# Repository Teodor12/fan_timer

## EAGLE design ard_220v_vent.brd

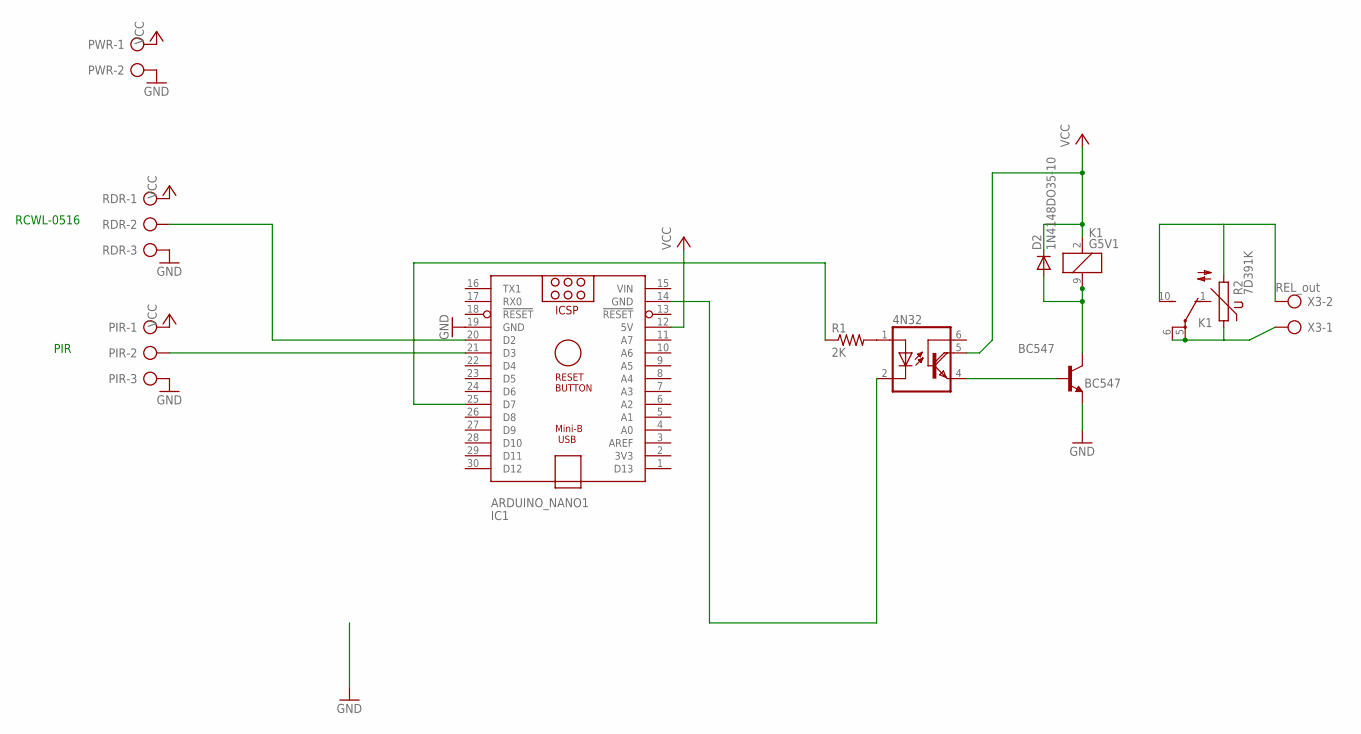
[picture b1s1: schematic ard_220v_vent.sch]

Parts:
4N32: 4N33; DIL06; MPN 4N32
ARDUINO_NANO1: IC1; ARDUINO_NANO
BC547: BC547; TO92
D2: 1N4148DO35-10; DO35-10
K1: G5V1
PIR: AK500/3
PWR: AK500/2
R1: 2K; 0207/10
R2: 7D391K; S07K385
RDR: AK500/3
X3: REL_out; AK500/2

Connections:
GND: ARDUINO_NANO1.19 (GND), BC547.1 (E), PIR.3, PWR.2, RDR.3
unnamed: BC547.3 (C), D2.A, K1.9 (2)
unnamed: 4N32.1 (A), R1.2
unnamed: ARDUINO_NANO1.25 (D7), R1.1
unnamed: K1.10 (S), R2.2, X3.2
unnamed: 4N32.4 (E), BC547.2 (B)
unnamed: K1.5, K1.6, R2.1, X3.1
unnamed: ARDUINO_NANO1.21 (D3), PIR.2
unnamed: ARDUINO_NANO1.20 (D2), RDR.2
unnamed: 4N32.2 (C), ARDUINO_NANO1.14 (GND)
VCC: 4N32.5 (COL), ARDUINO_NANO1.12 (5V), D2.C, K1.2 (1), PIR.1, PWR.1, RDR.1
VIN: ARDUINO_NANO1.15 (VIN)

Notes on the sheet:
RCWL-0516
PIR

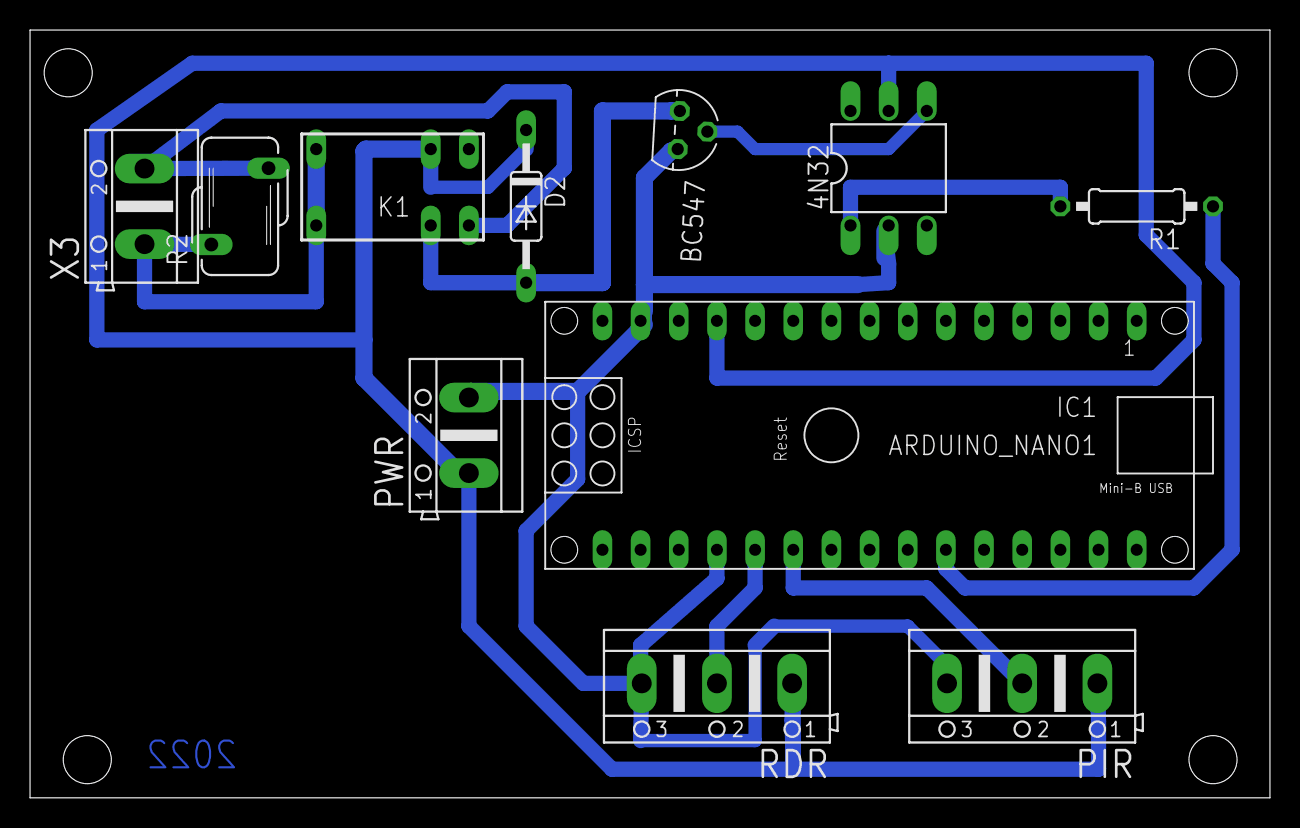
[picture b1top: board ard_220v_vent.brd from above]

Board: 2 copper layers, 82.5 x 51.1 mm, 11 parts (0 on the bottom side), 11 nets.
